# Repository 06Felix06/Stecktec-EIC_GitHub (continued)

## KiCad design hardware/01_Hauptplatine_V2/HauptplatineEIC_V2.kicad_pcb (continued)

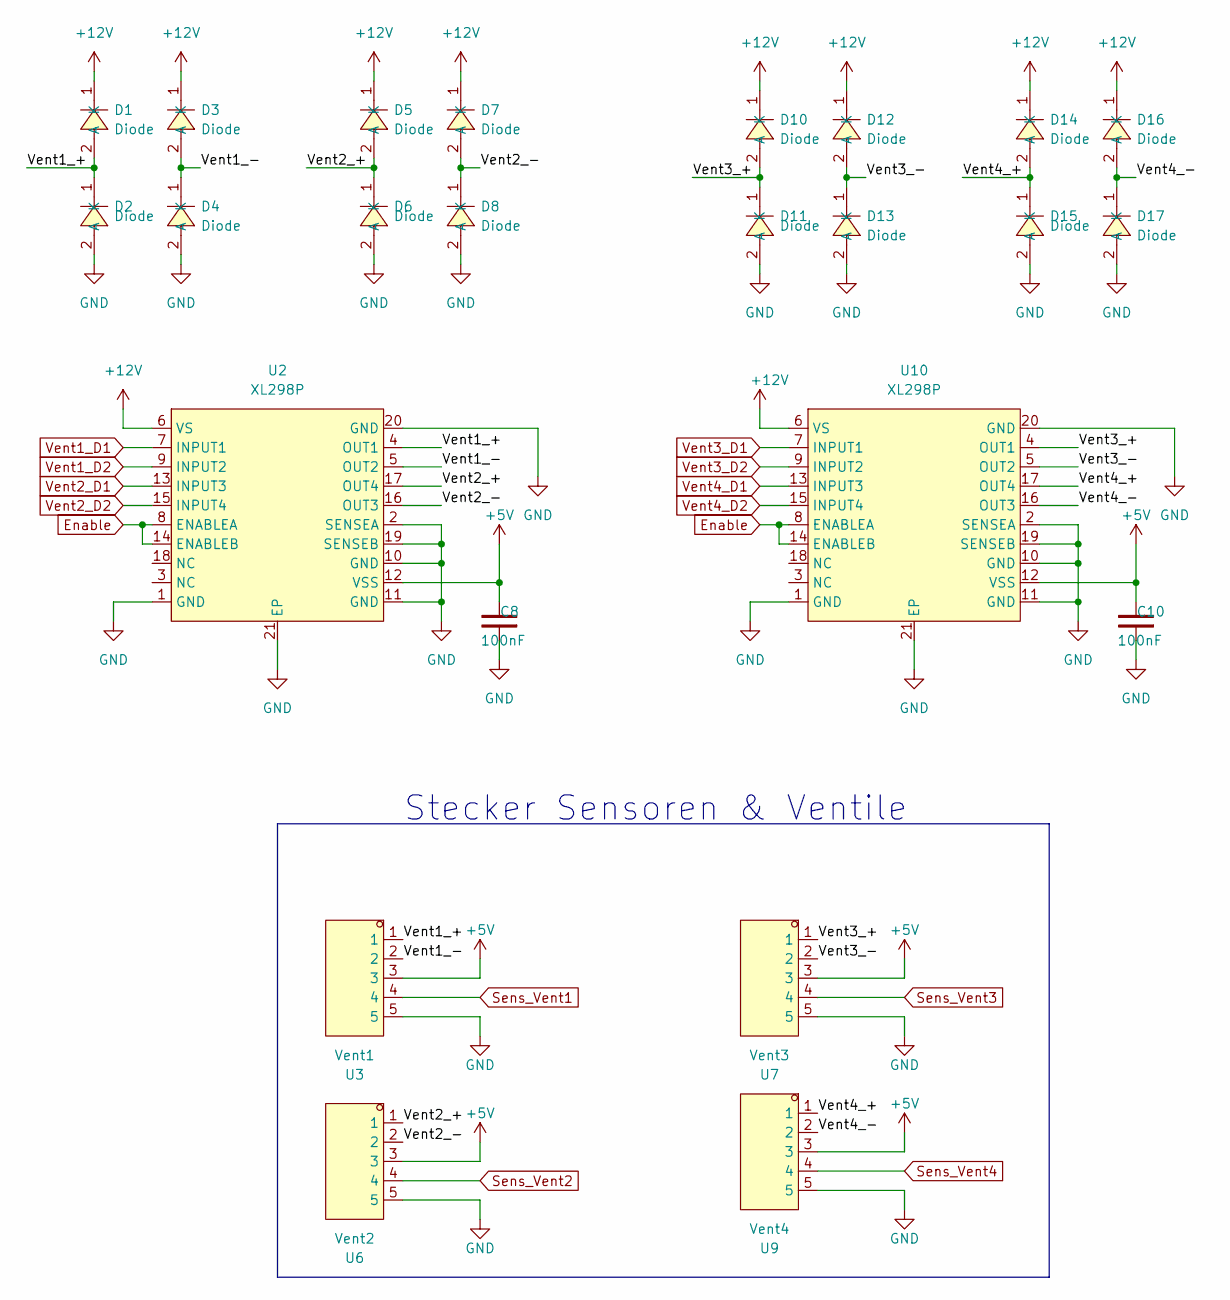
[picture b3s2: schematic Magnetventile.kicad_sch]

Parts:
C8, C10: 100nF; C_0805_2012Metric
D1, D2, D3, D4, D5, D6, D7, D8, D10, D11, D12, D13, D14, D15, D16, D17: Diode; SMA_L4.3-W2.5-LS5.0-RD; LCSC Part C727081
U2, U10: XL298P; HSOP-20_L15.9-W11.0-P1.27-LS14.2-BL-EP; LCSC Part C17179540
U3: Vent1; CONN-TH_B5B-PH-K-S-LF-SN; LCSC Part C157993
U6: Vent2; CONN-TH_B5B-PH-K-S-LF-SN; LCSC Part C157993
U7: Vent3; CONN-TH_B5B-PH-K-S-LF-SN; LCSC Part C157993
U9: Vent4; CONN-TH_B5B-PH-K-S-LF-SN; LCSC Part C157993

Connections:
+5V: C8.1, C10.1, U2.12 (VSS), U3.3, U6.3, U7.3, U9.3, U10.12 (VSS); also elsewhere on the board
+12V: D1.1 (K), D3.1 (K), D5.1 (K), D7.1 (K), D10.1 (K), D12.1 (K), D14.1 (K), D16.1 (K), U2.6 (VS), U10.6 (VS); also elsewhere on the board
/Magnetventile/Vent1_+: D1.2 (A), D2.1 (K), U2.4 (OUT1), U3.1
/Magnetventile/Vent1_-: D3.2 (A), D4.1 (K), U2.5 (OUT2), U3.2
/Magnetventile/Vent2_+: D5.2 (A), D6.1 (K), U2.17 (OUT4), U6.1
/Magnetventile/Vent2_-: D7.2 (A), D8.1 (K), U2.16 (OUT3), U6.2
/Magnetventile/Vent3_+: D10.2 (A), D11.1 (K), U7.1, U10.4 (OUT1)
/Magnetventile/Vent3_-: D12.2 (A), D13.1 (K), U7.2, U10.5 (OUT2)
/Magnetventile/Vent4_+: D14.2 (A), D15.1 (K), U9.1, U10.17 (OUT4)
/Magnetventile/Vent4_-: D16.2 (A), D17.1 (K), U9.2, U10.16 (OUT3)
Enable: U2.8 (ENABLEA), U2.14 (ENABLEB), U10.8 (ENABLEA), U10.14 (ENABLEB); also elsewhere on the board
GND: C8.2, C10.2, D2.2 (A), D4.2 (A), D6.2 (A), D8.2 (A), D11.2 (A), D13.2 (A), D15.2 (A), D17.2 (A), U2.1 (GND), U2.2 (SENSEA), U2.10 (GND), U2.11 (GND), U2.19 (SENSEB), U2.20 (GND), U2.21 (EP), U3.5, U6.5, U7.5, U9.5, U10.1 (GND), U10.2 (SENSEA), U10.10 (GND), U10.11 (GND), U10.19 (SENSEB), U10.20 (GND), U10.21 (EP); also elsewhere on the board
Sens_Vent1: U3.4; also elsewhere on the board
Sens_Vent2: U6.4; also elsewhere on the board
Sens_Vent3: U7.4; also elsewhere on the board
Sens_Vent4: U9.4; also elsewhere on the board
Vent1_D1: U2.7 (INPUT1); also elsewhere on the board
Vent1_D2: U2.9 (INPUT2); also elsewhere on the board
Vent2_D1: U2.13 (INPUT3); also elsewhere on the board
Vent2_D2: U2.15 (INPUT4); also elsewhere on the board
Vent3_D1: U10.7 (INPUT1); also elsewhere on the board
Vent3_D2: U10.9 (INPUT2); also elsewhere on the board
Vent4_D1: U10.13 (INPUT3); also elsewhere on the board
Vent4_D2: U10.15 (INPUT4); also elsewhere on the board

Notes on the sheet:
Stecker Sensoren & Ventile

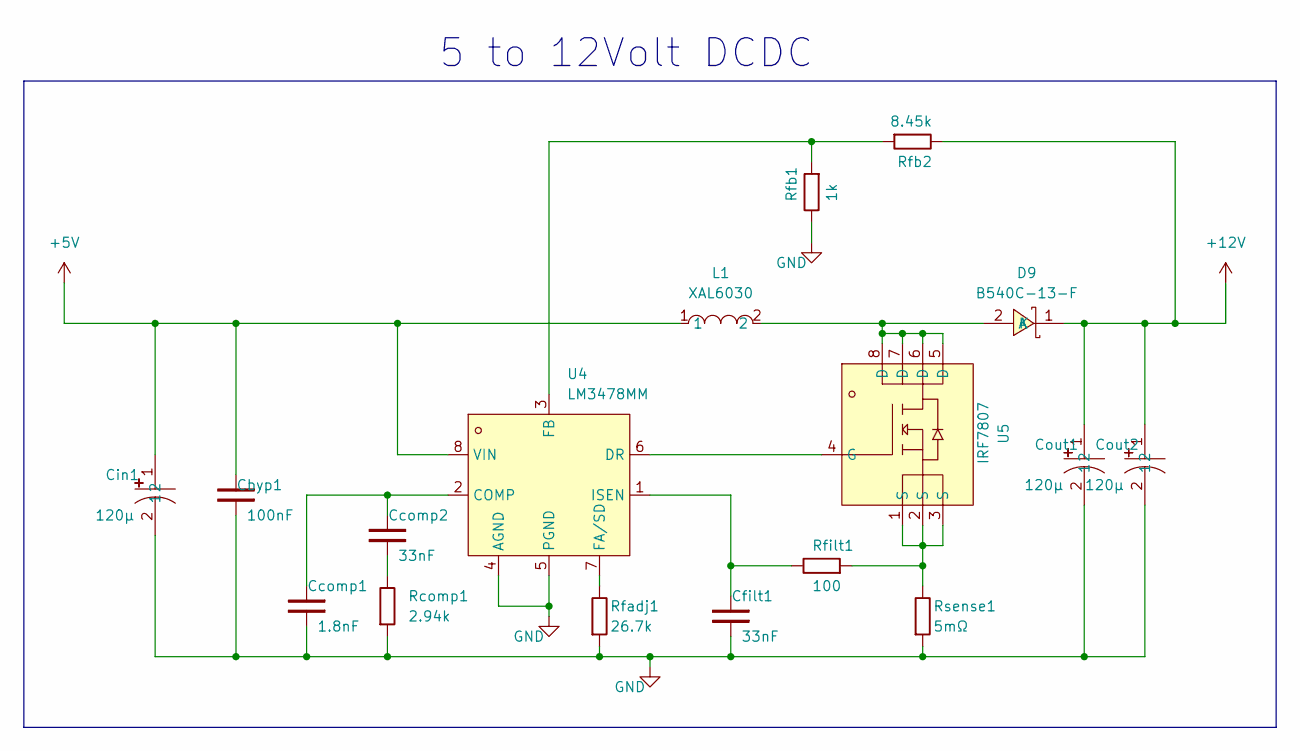
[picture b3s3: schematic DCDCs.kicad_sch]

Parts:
Cbyp1: 100nF; C_0805_2012Metric
Ccomp1: 1.8nF; C_0805_2012Metric
Ccomp2: 33nF; C_0805_2012Metric
Cfilt1: 33nF; C_0805_2012Metric
Cin1: 120µ; CAP-TH_BD6.3-P2.50-D1.0-FD; LCSC Part C442997
Cout1, Cout2: 120µ; CAP-TH_BD6.3-P2.50-D1.0-FD; LCSC Part C442997
D9: B540C-13-F; SMC_L7.1-W6.2-LS8.1-RD; LCSC Part C72264
L1: XAL6030; IND-SMD_L6.6-W6.4; LCSC Part C19191693
Rcomp1: 2.94k; R_0805_2012Metric
Rfadj1: 26.7k; R_0805_2012Metric
Rfb1: 1k; R_0805_2012Metric
Rfb2: 8.45k; R_0805_2012Metric
Rfilt1: 100; R_0805_2012Metric
Rsense1: 5mΩ; R_0805_2012Metric
U4: LM3478MM; VSSOP-8_L3.0-W3.0-P0.65-LS5.0-BL; LCSC Part C9404
U5: IRF7807; SOP-8_L4.9-W3.9-P1.27-LS6.0-BL; LCSC Part C5350865

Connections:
+5V: Cbyp1.1, Cin1.1, L1.1, U4.8 (VIN); also elsewhere on the board
+12V: Cout1.1, Cout2.1, D9.1 (K), Rfb2.2; also elsewhere on the board
GND: Cbyp1.2, Ccomp1.2, Cfilt1.2, Cin1.2, Cout1.2, Cout2.2, Rcomp1.1, Rfadj1.1, Rfb1.2, Rsense1.1, U4.4 (AGND), U4.5 (PGND); also elsewhere on the board
unnamed: Ccomp2.2, Rcomp1.2
unnamed: D9.2 (A), L1.2, U5.5 (D), U5.6 (D), U5.7 (D), U5.8 (D)
unnamed: Rfilt1.1, Rsense1.2, U5.1 (S), U5.2 (S), U5.3 (S)
unnamed: Ccomp1.1, Ccomp2.1, U4.2 (COMP)
unnamed: U4.6 (DR), U5.4 (G)
unnamed: Rfadj1.2, U4.7 (FA/SD)
unnamed: Rfb1.1, Rfb2.1, U4.3 (FB)
unnamed: Cfilt1.1, Rfilt1.2, U4.1 (ISEN)

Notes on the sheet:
5 to 12Volt DCDC

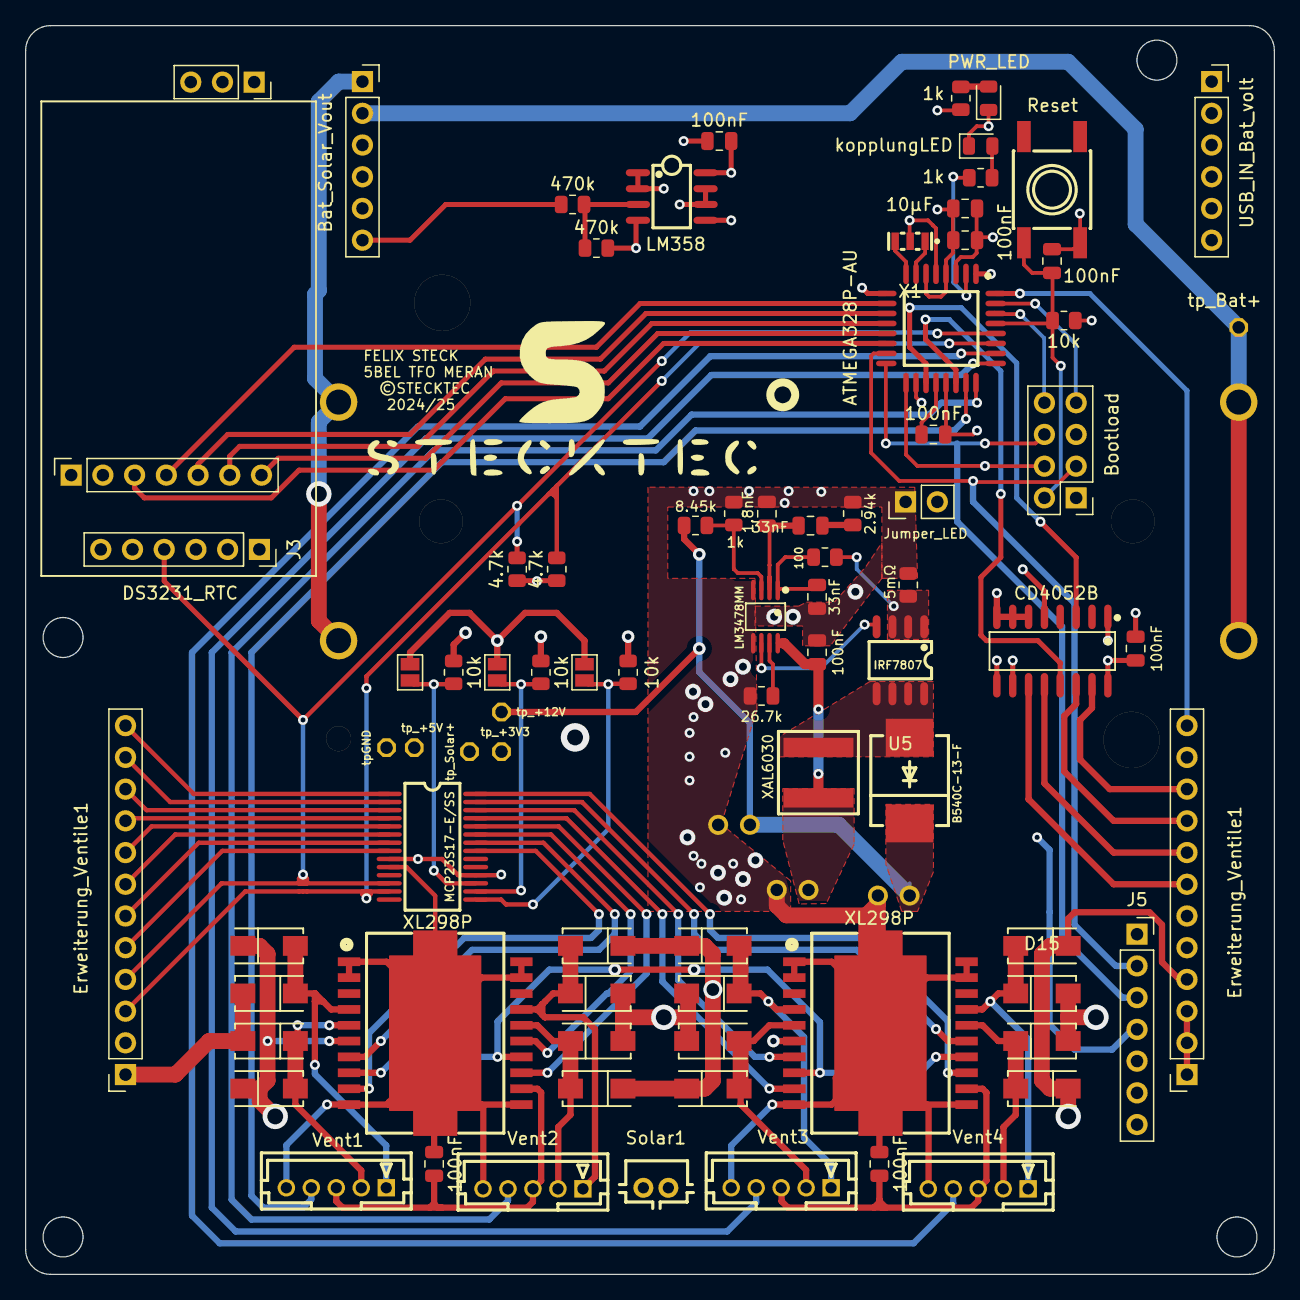
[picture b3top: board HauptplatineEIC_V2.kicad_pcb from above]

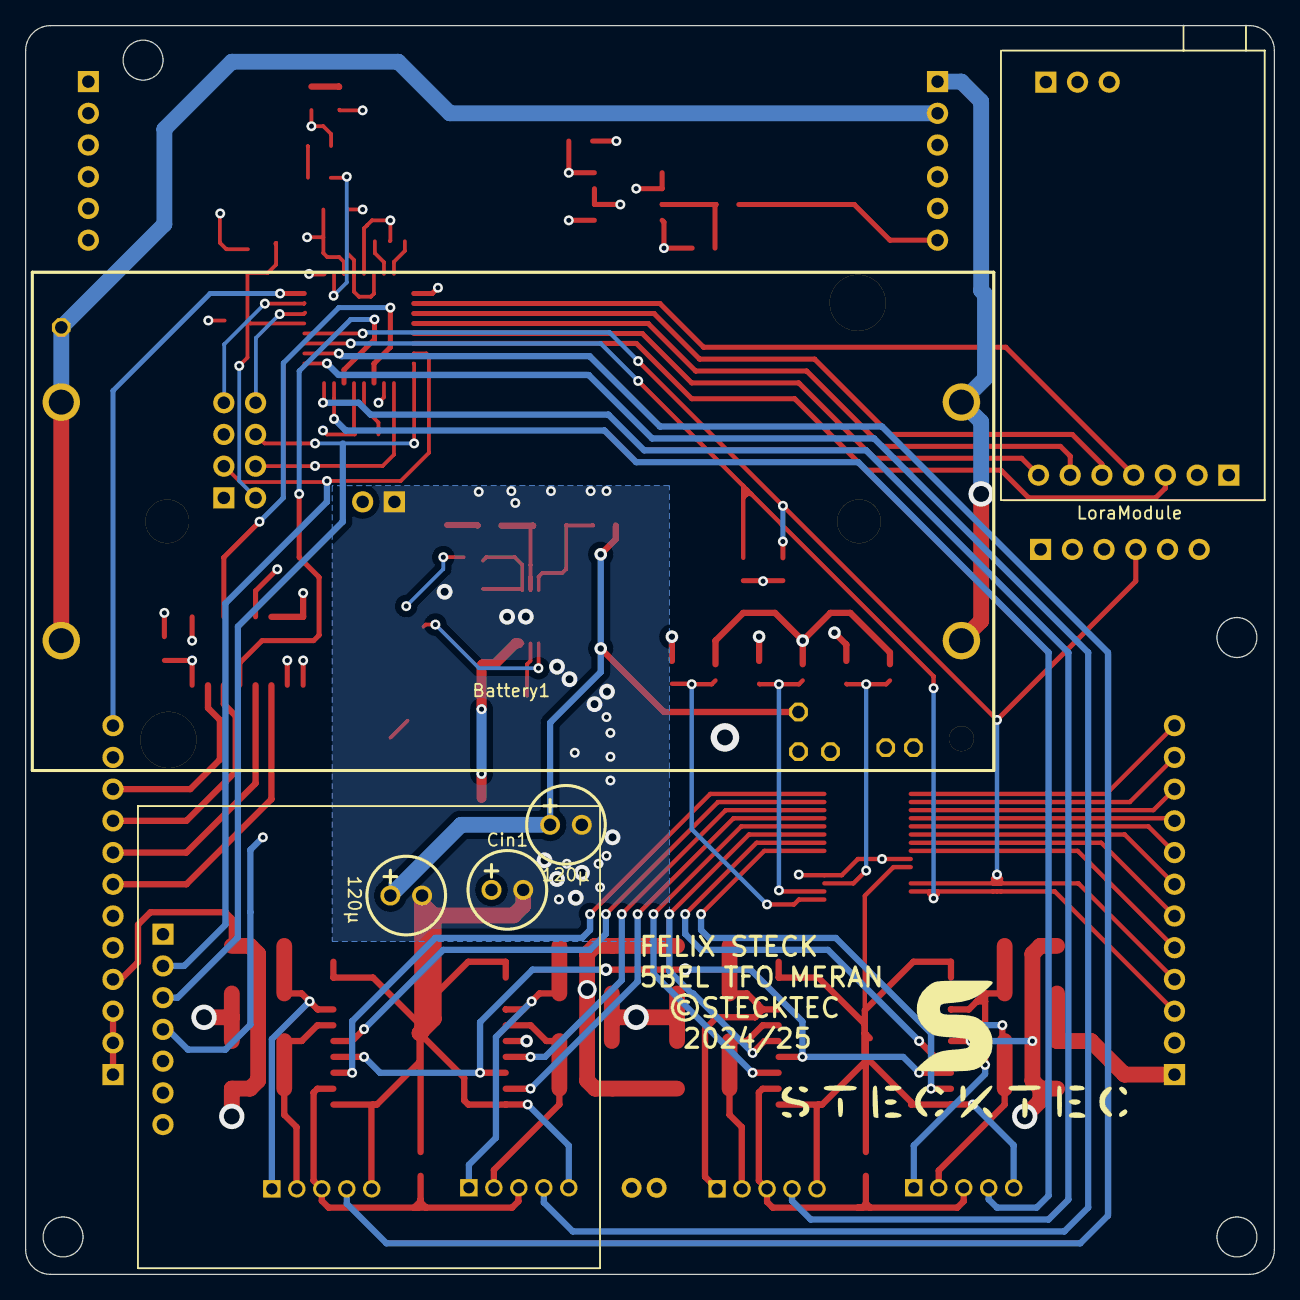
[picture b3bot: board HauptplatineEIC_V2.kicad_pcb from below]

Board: 6 copper layers, 100.0 x 100.0 mm, 86 parts (4 on the bottom side), 80 nets.

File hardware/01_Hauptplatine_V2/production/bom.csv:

Designator,Footprint,Quantity,Value,LCSC Part #
Battery1,BAT-TH_L77.0-W39.9_BH-18650-A1BJ021,1,BH-18650-A1BJ021,C20606804
"C1, C10, C2, C4, C5, C6, C8, Cbyp1",0805,8,100nF,
C3,0805,1,10µF,
Ccomp1,0805,1,1.8nF,
"Ccomp2, Cfilt1",0805,2,33nF,
"Cin1, Cout1, Cout2",CAP-TH_BD6.3-P2.50-D1.0-FD,3,120µ,C442997
"D1, D10, D11, D12, D13, D14, D15, D16, D17, D2, D3, D4, D5, D6, D7, D8",SMA_L4.3-W2.5-LS5.0-RD,16,Diode,C727081
D30,0805,1,kopplungLED,
D31,0805,1,PWR_LED,
D9,SMC_L7.1-W6.2-LS8.1-RD,1,B540C-13-F,C72264
J1,PinSocket_1x07_P2.54mm_Vertical,1,LoraModule,
J15,PinHeader_1x02_P2.54mm_Vertical,1,Jumper_LED,
J17,PinSocket_1x03_P2.54mm_Vertical,1,Befestigung,
J2,PinHeader_2x04_P2.54mm_Vertical,1,Bootload,
"J20, J4",PinSocket_1x12_P2.54mm_Vertical,2,Erweiterung_Ventile1,
J3,PinSocket_1x06_P2.54mm_Vertical,1,DS3231_RTC,
J5,PinSocket_1x07_P2.54mm_Vertical,1,Sim7000,
J7,PinSocket_1x06_P2.54mm_Vertical,1,USB_IN_Bat_volt,
J8,PinSocket_1x06_P2.54mm_Vertical,1,Bat_Solar_Vout,
"JP4, JP5, JP6",SolderJumper-2_P1.3mm_Open_Pad1.0x1.5mm,3,SolderJumper_2_Open,
L1,IND-SMD_L6.6-W6.4,1,XAL6030,C19191693
"R1, R6, R7, R8",0805,4,10k,
"R2, R3",0805,2,470k,
"R4, R5",0805,2,4.7k,
"RV_LED1, RV_LED2, Rfb1",0805,3,1k,
Rcomp1,0805,1,2.94k,
Reset1,SW-SMD_4P-L6.2-W6.2-P4.50-LS8.6,1,Reset,C2909692
Rfadj1,0805,1,26.7k,
Rfb2,0805,1,8.45k,
Rfilt1,0805,1,100,
Rsense1,0805,1,5mΩ,
Solar1,CONN-TH_B2B-PH-K-S,1,B2B-PH-K-S(LF)(SN),C131337
TP1,TPSteckFelix,1,tp_Bat+,
TP2,TPSteckFelix,1,tp_Solar+,
TP3,TPSteckFelix,1,tp_+5V,
TP4,TPSteckFelix,1,tp_+3V3,
TP5,TPSteckFelix,1,tpGND,
TP6,TPSteckFelix,1,tp_+12V,
U1,TQFP-32_L7.0-W7.0-P0.80-LS9.0-BL,1,ATMEGA328P-AU,C14877
"U10, U2",HSOP-20_L15.9-W11.0-P1.27-LS14.2-BL-EP,2,XL298P,C17179540
U11,SOIC-8_L5.0-W4.0-P1.27-LS6.0-BL,1,LM358,
U12,SSOP-28_L10.2-W5.3-P0.65-LS7.8-BL,1,MCP23S17-E/SS,C148009
U3,CONN-TH_B5B-PH-K-S-LF-SN,1,Vent1,C157993
U4,VSSOP-8_L3.0-W3.0-P0.65-LS5.0-BL,1,LM3478MM,C9404
U5,SOP-8_L4.9-W3.9-P1.27-LS6.0-BL,1,IRF7807,C5350865
U6,CONN-TH_B5B-PH-K-S-LF-SN,1,Vent2,C157993
U7,CONN-TH_B5B-PH-K-S-LF-SN,1,Vent3,C157993
U8,SOIC-16_L9.9-W3.9-P1.27-LS6.0-BL,1,CD4052B,C5356105
U9,CONN-TH_B5B-PH-K-S-LF-SN,1,Vent4,C157993
X1,OSC-SMD_3P-L3.2-W1.3-P1.20-L,1,CSTNE16M0V53Z000R0,C783275

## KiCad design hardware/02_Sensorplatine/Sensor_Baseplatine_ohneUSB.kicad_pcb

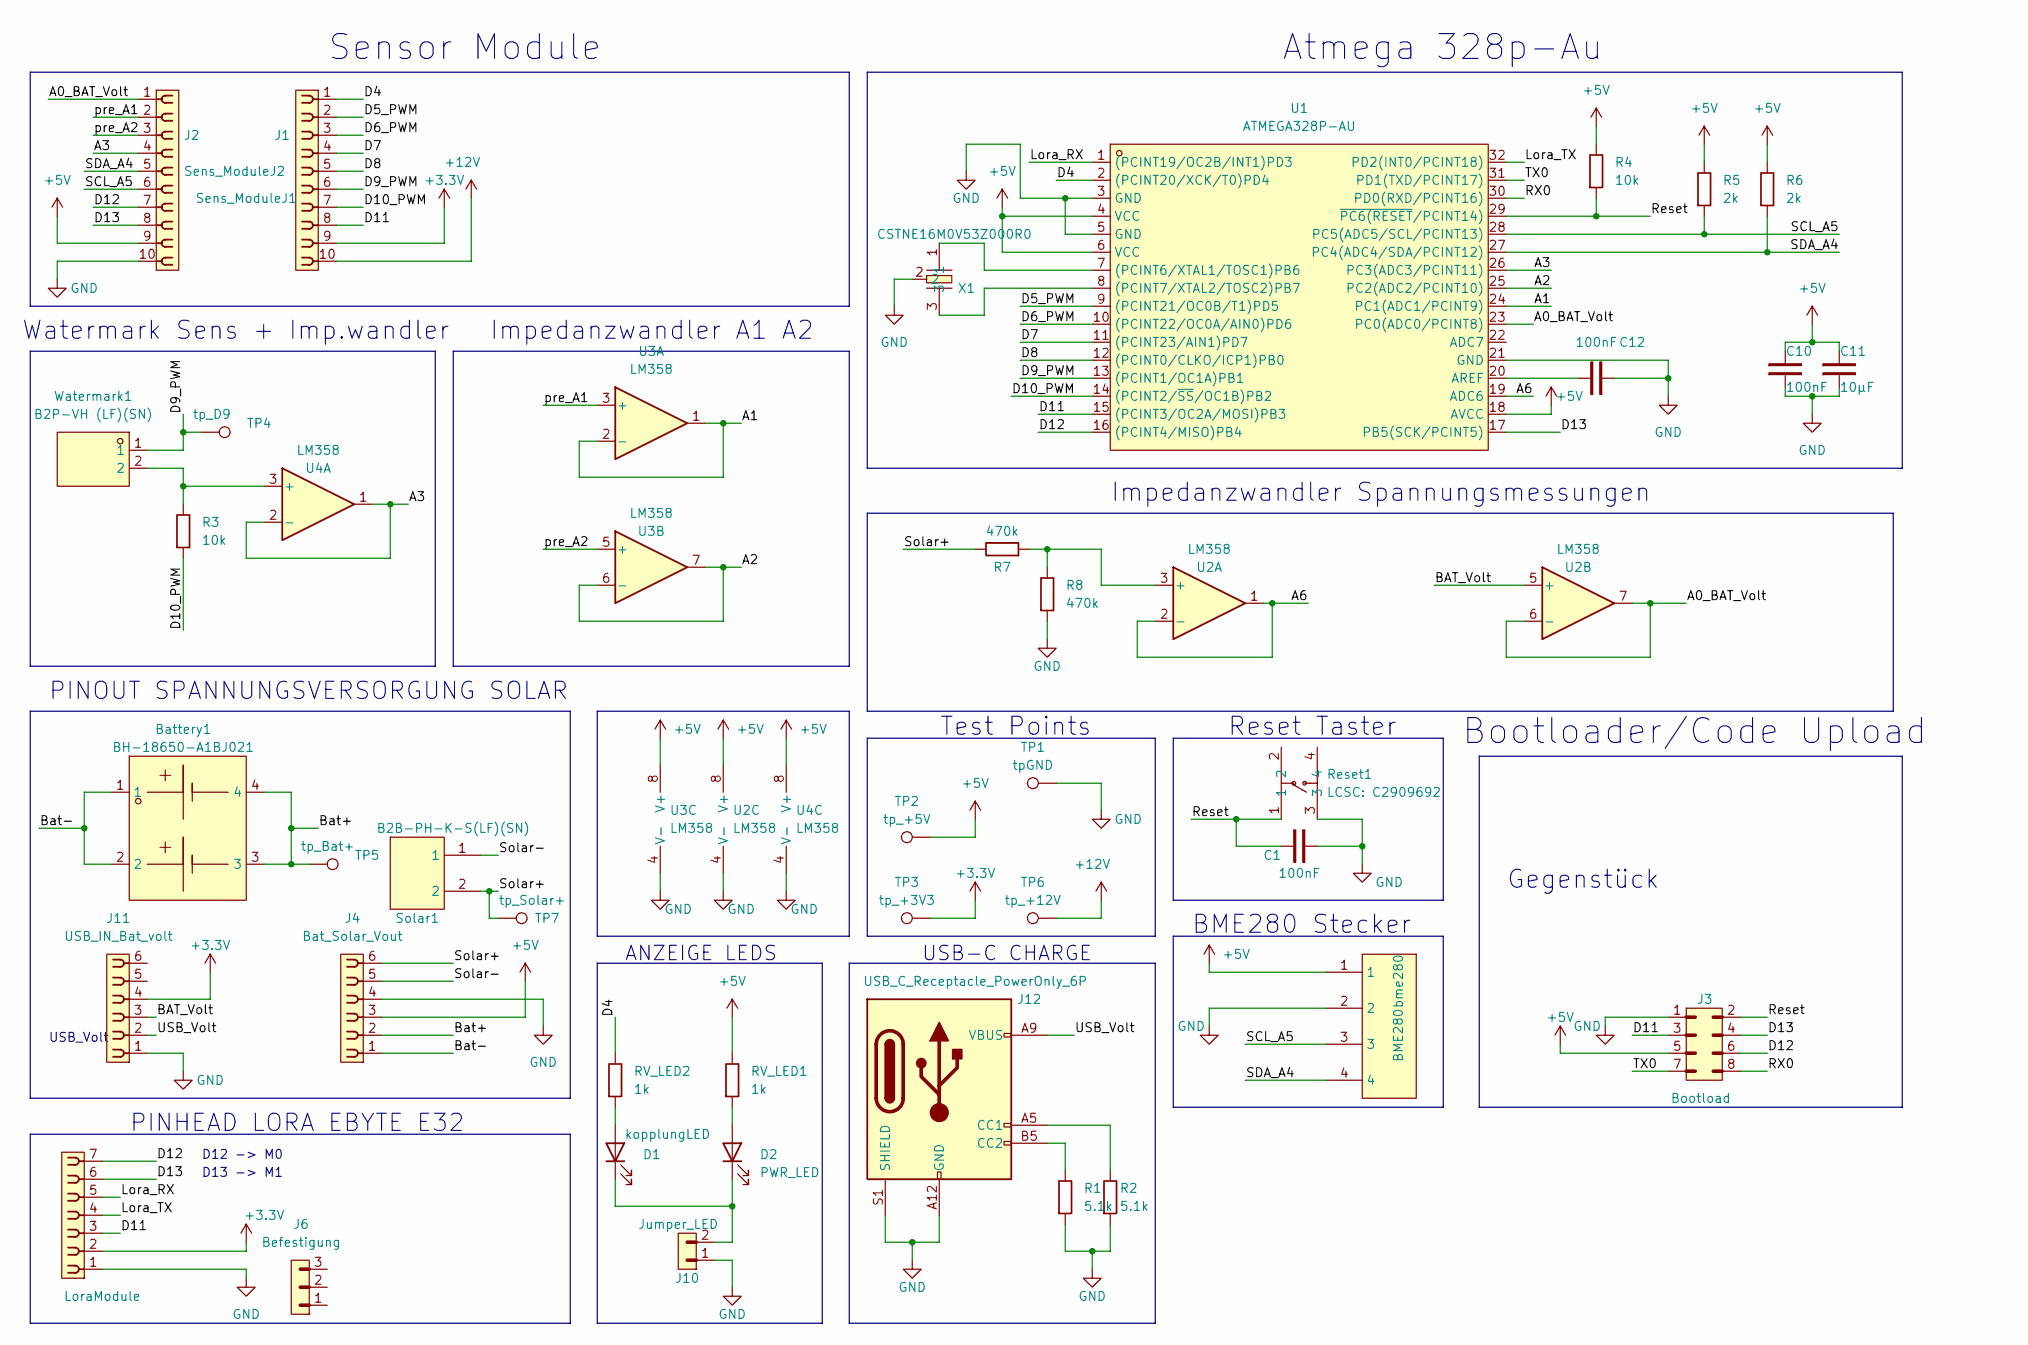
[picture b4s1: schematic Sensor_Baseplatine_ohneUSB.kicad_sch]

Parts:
Battery1: BH-18650-A1BJ021; BAT-TH_L77.0-W39.9_BH-18650-A1BJ021; LCSC Part C20606804
C1, C10, C12: 100nF; C_0805_2012Metric
C11: 10µF; C_0805_2012Metric
D1: kopplungLED; LED_0805_2012Metric
D2: PWR_LED; LED_0805_2012Metric
J1: Sens_ModuleJ1; PinSocket_1x10_P2.54mm_Vertical
J2: Sens_ModuleJ2; PinSocket_1x10_P2.54mm_Vertical
J3: Bootload; PinHeader_2x04_P2.54mm_Vertical
J4: Bat_Solar_Vout; PinSocket_1x06_P2.54mm_Vertical
J5: LoraModule; PinSocket_1x07_P2.54mm_Vertical
J6: Befestigung; PinHeader_1x03_P2.54mm_Vertical
J10: Jumper_LED; PinHeader_1x02_P2.54mm_Vertical
J11: USB_IN_Bat_volt; PinSocket_1x06_P2.54mm_Vertical
J12: USB_C_Receptacle_PowerOnly_6P; USB_C_Receptacle_GCT_USB4125-xx-x_6P_TopMnt_Horizontal
R1, R2: 5.1k; R_0805_2012Metric
R3, R4: 10k; R_0805_2012Metric
R5, R6: 2k; R_0805_2012Metric
R7, R8: 470k; R_0805_2012Metric
RV_LED1, RV_LED2: 1k; R_0805_2012Metric
Reset1: LCSC: C2909692; SW-SMD_4P-L6.2-W6.2-P4.50-LS8.6; LCSC Part C2909692
Solar1: B2B-PH-K-S(LF)(SN); CONN-TH_B2B-PH-K-S; LCSC Part C131337
TP1: tpGND; TPSteckFelix
TP2: tp_+5V; TPSteckFelix
TP3: tp_+3V3; TPSteckFelix
TP4: tp_D9; TPSteckFelix
TP5: tp_Bat+; TPSteckFelix
TP6: tp_+12V; TPSteckFelix
TP7: tp_Solar+; TPSteckFelix
U1: ATMEGA328P-AU; TQFP-32_L7.0-W7.0-P0.80-LS9.0-BL; LCSC Part C14877
U2, U3, U4: LM358; SOIC-8_L5.0-W4.0-P1.27-LS6.0-BL
Watermark1: B2P-VH (LF)(SN); CONN-TH_B2P-VH-LF-SN; LCSC Part C160315
X1: CSTNE16M0V53Z000R0; OSC-SMD_3P-L3.2-W1.3-P1.20-L; LCSC Part C783275
bme280: BME280; CONN-TH_B4B-PH-K-S; LCSC Part C131334

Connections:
+3.3V: J1.9, J5.2, J11.4, TP3.1
+5V: C10.2, C11.2, J2.9, J3.5, J4.3, R4.2, R5.2, R6.2, RV_LED1.2, TP2.1, U1.4 (VCC), U1.6 (VCC), U1.18 (AVCC), U2.8 (V+), U3.8 (V+), U4.8 (V+), bme280.1
+12V: J1.10, TP6.1
/A0_BAT_Volt: J2.1, U1.23 (PC0(ADC0/PCINT8)), U2.6 (-), U2.7
/A1: U1.24 (PC1(ADC1/PCINT9)), U3.1, U3.2 (-)
/A2: U1.25 (PC2(ADC2/PCINT10)), U3.6 (-), U3.7
/A3: J2.4, U1.26 (PC3(ADC3/PCINT11)), U4.1, U4.2 (-)
/A6: U1.19 (ADC6), U2.1, U2.2 (-)
/BAT_Volt: J11.3, U2.5 (+)
/Bat+: Battery1.3, Battery1.4, J4.2, TP5.1
/Bat-: Battery1.1, Battery1.2, J4.1
/D4: J1.1, RV_LED2.2, U1.2 ((PCINT20/XCK/T0)PD4)
/D5_PWM: J1.2, U1.9 ((PCINT21/OC0B/T1)PD5)
/D6_PWM: J1.3, U1.10 ((PCINT22/OC0A/AIN0)PD6)
/D7: J1.4, U1.11 ((PCINT23/AIN1)PD7)
/D8: J1.5, U1.12 ((PCINT0/CLKO/ICP1)PB0)
/D9_PWM: J1.6, TP4.1, U1.13 ((PCINT1/OC1A)PB1), Watermark1.1
/D10_PWM: J1.7, R3.1, U1.14 ((PCINT2/~SS/OC1B)PB2)
/D11: J1.8, J3.3, J5.3, U1.15 ((PCINT3/OC2A/MOSI)PB3)
/D12: J2.7, J3.6, J5.7, U1.16 ((PCINT4/MISO)PB4)
/D13: J2.8, J3.4, J5.6, U1.17 (PB5(SCK/PCINT5))
/Lora_RX: J5.5, U1.1 ((PCINT19/OC2B/INT1)PD3)
/Lora_TX: J5.4, U1.32 (PD2(INT0/PCINT18))
/RX0: J3.8, U1.30 (PD0(RXD/PCINT16))
/Reset: C1.1, J3.2, R4.1, Reset1.1, U1.29 (~PC6(RESET/PCINT14))
/SCL_A5: J2.6, R5.1, U1.28 (PC5(ADC5/SCL/PCINT13)), bme280.3
/SDA_A4: J2.5, R6.1, U1.27 (PC4(ADC4/SDA/PCINT12)), bme280.4
/Solar+: J4.6, R7.2, Solar1.2, TP7.1
/Solar-: J4.5, Solar1.1
/TX0: J3.7, U1.31 (PD1(TXD/PCINT17))
/USB_Volt: J11.2, J12.A9 (VBUS), J12.B9 (VBUS)
/pre_A1: J2.2, U3.3 (+)
/pre_A2: J2.3, U3.5 (+)
GND: C1.2, C10.1, C11.1, C12.1, J2.10, J3.1, J4.4, J5.1, J10.1, J11.1, J12.A12 (GND), J12.B12 (GND), J12.S1 (SHIELD), R1.1, R2.1, R8.1, Reset1.3, TP1.1, U1.3 (GND), U1.5 (GND), U1.21 (GND), U2.4 (V-), U3.4 (V-), U4.4 (V-), X1.2, bme280.2
unnamed: D1.2 (A), RV_LED2.1
unnamed: D1.1 (K), D2.1 (K), J10.2
unnamed: D2.2 (A), RV_LED1.1
unnamed: J12.A5 (CC1), R2.2
unnamed: J12.B5 (CC2), R1.2
unnamed: U1.7 ((PCINT6/XTAL1/TOSC1)PB6), X1.1
unnamed: U1.8 ((PCINT7/XTAL2/TOSC2)PB7), X1.3
unnamed: C12.2, U1.20 (AREF)
unnamed: R7.1, R8.2, U2.3 (+)
unnamed: R3.2, U4.3 (+), Watermark1.2

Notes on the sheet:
Gegenstück
Atmega 328p-Au
PINHEAD LORA EBYTE E32
USB-C CHARGE
Impedanzwandler Spannungsmessungen
Reset Taster
Watermark Sens + Imp.wandler
PINOUT SPANNUNGSVERSORGUNG SOLAR
D13 -> M1
Sensor Module
ANZEIGE LEDS
Bootloader/Code Upload
USB_Volt
Test Points
D12 -> M0
Impedanzwandler A1 A2
BME280 Stecker

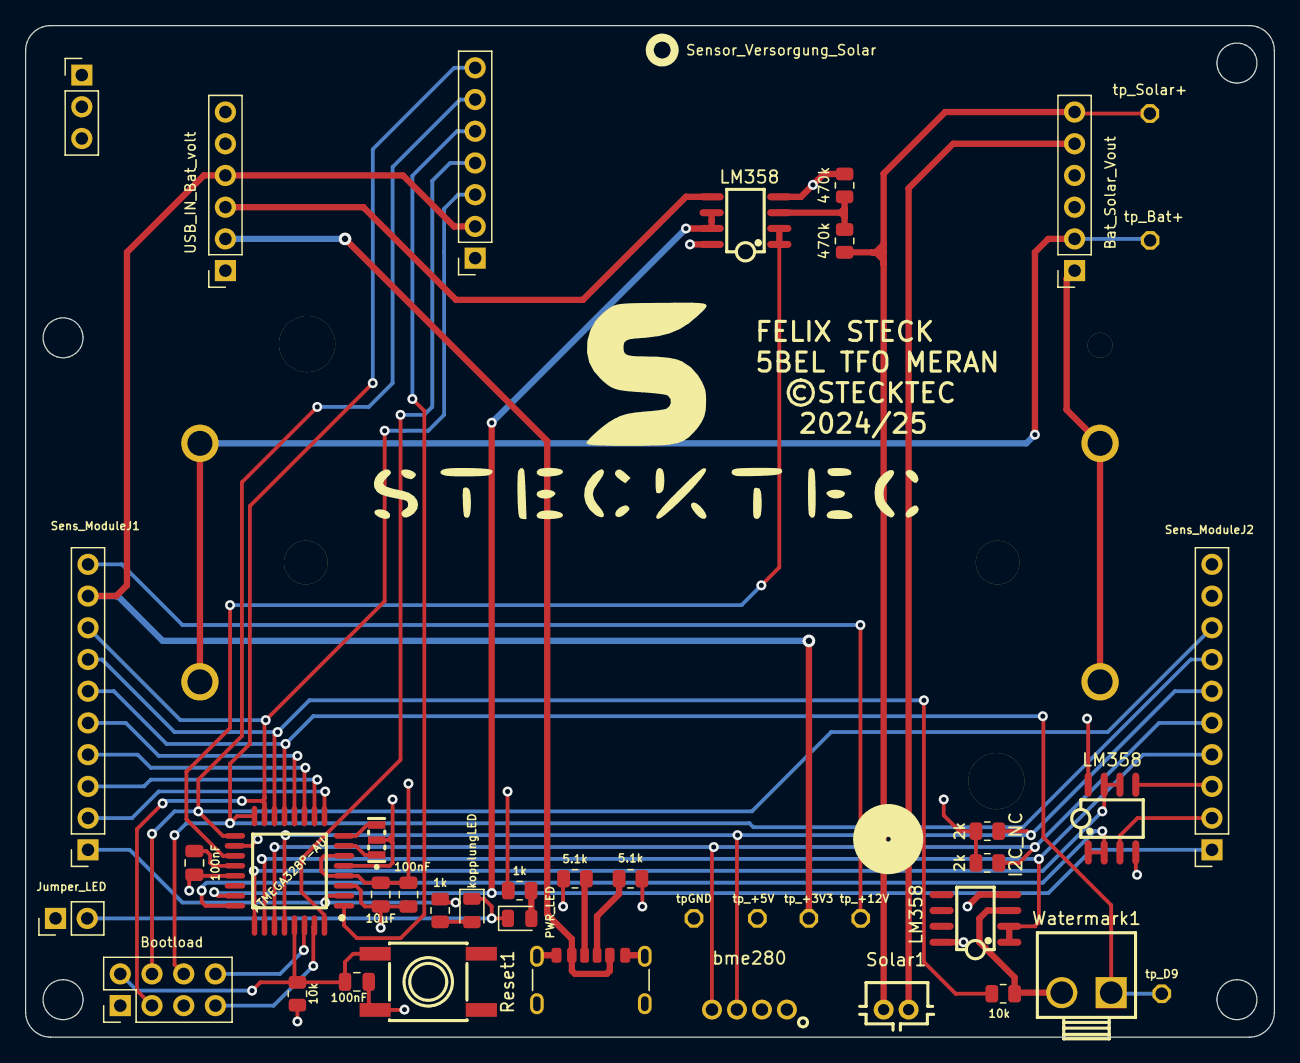
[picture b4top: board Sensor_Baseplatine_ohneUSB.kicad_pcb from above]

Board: 4 copper layers, 100.0 x 81.0 mm, 42 parts (1 on the bottom side), 44 nets.

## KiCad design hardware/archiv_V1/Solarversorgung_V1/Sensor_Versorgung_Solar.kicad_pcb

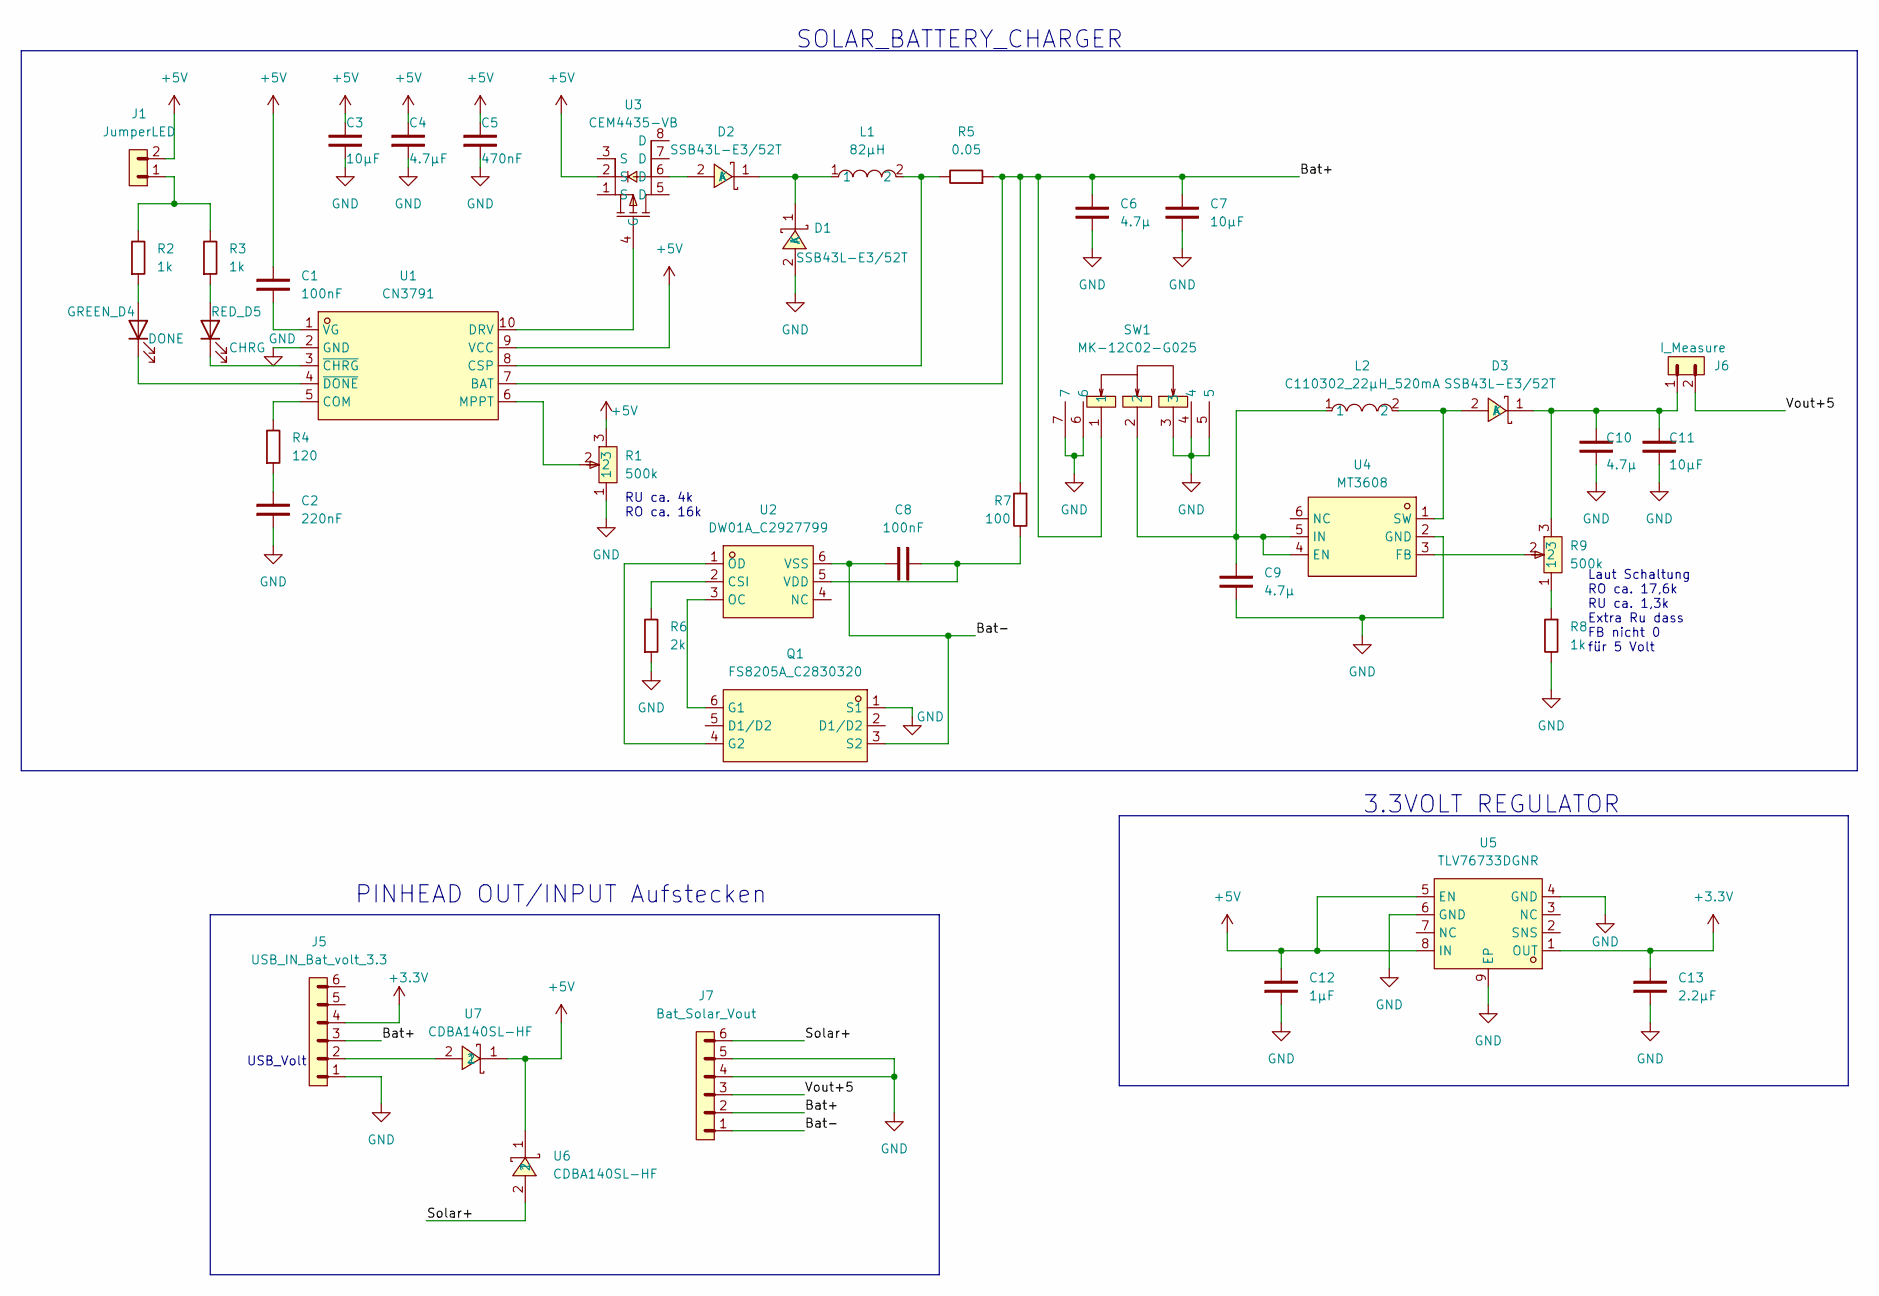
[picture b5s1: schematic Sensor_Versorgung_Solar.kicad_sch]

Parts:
C1, C8: 100nF; C_0805_2012Metric
C2: 220nF; C_0805_2012Metric
C3, C7, C11: 10µF; C_0805_2012Metric
C4: 4.7µF; C_0805_2012Metric
C5: 470nF; C_0805_2012Metric
C6, C9, C10: 4.7µ; C_0805_2012Metric
C12: 1µF; C_0805_2012Metric
C13: 2.2µF; C_0805_2012Metric
D1, D2, D3: SSB43L-E3/52T; SMB_L4.6-W3.6-LS5.3-RD; LCSC Part C222519
GREEN_D4: DONE; LED_0805_2012Metric
J1: JumperLED; PinHeader_1x02_P2.54mm_Vertical
J5: USB_IN_Bat_volt_3.3; PinHeader_1x06_P2.54mm_Vertical
J6: I_Measure; PinHeader_1x02_P2.54mm_Vertical
J7: Bat_Solar_Vout; PinHeader_1x06_P2.54mm_Vertical
L1: 82µH; IND-SMD_L3.5-W2.9_FHW1210IF820JST; LCSC Part C394099
L2: C110302_22µH_520mA; IND-SMD_L3.0-W3.0_LQH3NPN; LCSC Part C110302
Q1: FS8205A_C2830320; SOT-23-6_L2.9-W1.6-P0.95-LS2.8-BR; LCSC Part C2830320
R1, R9: 500k; RES-ADJ-SMD_VG039NCH; LCSC Part C128558
R2, R3, R8: 1k; R_0805_2012Metric
R4: 120; R_0805_2012Metric
R5: 0.05; R_0805_2012Metric
R6: 2k; R_0805_2012Metric
R7: 100; R_0805_2012Metric
RED_D5: CHRG; LED_0805_2012Metric
SW1: MK-12C02-G025; SW-SMD_MK-12C02-G025; LCSC Part C778186
U1: CN3791; SSOP-10_L4.9-W3.9-P1.00-LS6.0-BL; LCSC Part C154992
U2: DW01A_C2927799; SOT-23-6_L2.9-W1.6-P0.95-LS2.8-BL; LCSC Part C2927799
U3: CEM4435-VB; SOIC-8_L4.9-W3.9-P1.27-LS6.0-BL; LCSC Part C5137442
U4: MT3608; SOT-23-6_L2.9-W1.6-P0.95-LS2.8-BL; LCSC Part C84817
U5: TLV76733DGNR; MSOP-8_L3.0-W3.0-P0.65-LS4.9-BL-EP-1; LCSC Part C2873382
U6, U7: CDBA140SL-HF; DO-214AC_L4.3-W2.7-LS5.3-RD; LCSC Part C3012747

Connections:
+3.3V: C13.2, J5.4, U5.1 (OUT)
+5V: C1.2, C3.1, C4.2, C5.2, C12.2, J1.2, R1.3, U1.9 (VCC), U3.2 (S), U5.5 (EN), U5.8 (IN), U6.1, U7.1
/Bat+: C6.1, C7.1, J5.3, J7.2, R5.1, R7.1, SW1.1, U1.7 (BAT)
/Bat-: C8.1, J7.1, Q1.3 (S2), U2.6 (VSS)
/Solar+: J7.6, U6.2
/Vout+5: J6.2, J7.3
GND: C2.1, C3.2, C4.1, C5.1, C6.2, C7.2, C9.2, C10.2, C11.2, C12.1, C13.1, D1.2 (A), J5.1, J7.4, J7.5, Q1.1 (S1), R1.1, R6.1, R8.2, SW1.3, SW1.4, SW1.5, SW1.6, SW1.7, U1.2 (GND), U4.2 (GND), U5.4 (GND), U5.6 (GND), U5.9 (EP)
unnamed: C2.2, R4.1
unnamed: D1.1 (K), D2.1 (K), L1.1
unnamed: D2.2 (A), U3.6 (D)
unnamed: D3.2 (A), L2.2, U4.1 (SW)
unnamed: C10.1, C11.1, D3.1 (K), J6.1, R9.3
unnamed: GREEN_D4.2 (A), R2.1
unnamed: GREEN_D4.1 (K), U1.4 (~DONE)
unnamed: J1.1, R2.2, R3.2
unnamed: J5.2, U7.2
unnamed: Q1.6 (G1), U2.3 (OC)
unnamed: Q1.4 (G2), U2.1 (OD)
unnamed: R8.1, R9.1
unnamed: R3.1, RED_D5.2 (A)
unnamed: RED_D5.1 (K), U1.3 (~CHRG)
unnamed: R4.2, U1.5 (COM)
unnamed: L1.2, R5.2, U1.8 (CSP)
unnamed: U1.10 (DRV), U3.4 (G)
unnamed: R1.2, U1.6 (MPPT)
unnamed: C1.1, U1.1 (VG)
unnamed: R6.2, U2.2 (CSI)
unnamed: C8.2, R7.2, U2.5 (VDD)
unnamed: C9.1, L2.1, SW1.2, U4.4 (EN), U4.5 (IN)
unnamed: R9.2, U4.3 (FB)

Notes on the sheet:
PINHEAD OUT/INPUT Aufstecken
RU ca. 4k RO ca. 16k
SOLAR_BATTERY_CHARGER
Laut Schaltung RO ca. 17,6k RU ca. 1,3k Extra Ru dass FB nicht 0 für 5 Volt
3.3VOLT REGULATOR
USB_Volt

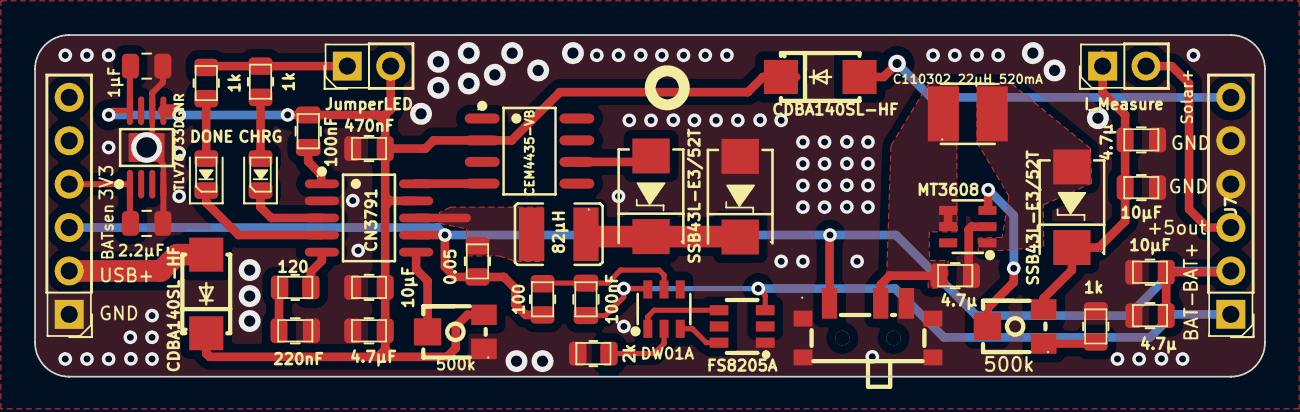
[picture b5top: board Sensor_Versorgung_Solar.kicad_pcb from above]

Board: 2 copper layers, 72.0 x 20.0 mm, 42 parts (0 on the bottom side), 30 nets.

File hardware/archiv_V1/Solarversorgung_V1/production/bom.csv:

Designator,Footprint,Quantity,Value,LCSC Part #
"C1, C8",0805,2,100nF,
"C10, C6, C9",0805,3,4.7µ,
"C11, C3, C7",0805,3,10µF,
C12,0805,1,1µF,
C13,0805,1,2.2µF,
C2,0805,1,220nF,
C4,0805,1,4.7µF,
C5,0805,1,470nF,
"D1, D2, D3",SMB_L4.6-W3.6-LS5.3-RD,3,SSB43L-E3/52T,C222519
GREEN_D4,0805,1,DONE,
J1,PinHeader_1x02_P2.54mm_Vertical,1,JumperLED,
J5,PinHeader_1x06_P2.54mm_Vertical,1,USB_IN_Bat_volt_3.3,
J6,PinHeader_1x02_P2.54mm_Vertical,1,I_Measure,
J7,PinHeader_1x06_P2.54mm_Vertical,1,Bat_Solar_Vout,
L1,IND-SMD_L3.5-W2.9_FHW1210IF820JST,1,82µH,C394099
L2,IND-SMD_L3.0-W3.0_LQH3NPN,1,C110302_22µH_520mA,C110302
Q1,SOT-23-6_L2.9-W1.6-P0.95-LS2.8-BR,1,FS8205A,C2830320
"R1, R9",RES-ADJ-SMD_VG039NCH,2,500k,C128558
"R2, R3, R8",0805,3,1k,
R4,0805,1,120,
R5,0805,1,0.05,
R6,0805,1,2k,
R7,0805,1,100,
RED_D5,0805,1,CHRG,
SW1,SW-SMD_MK-12C02-G025,1,MK-12C02-G025,C778186
U1,SSOP-10_L4.9-W3.9-P1.00-LS6.0-BL,1,CN3791,C154992
U2,SOT-23-6_L2.9-W1.6-P0.95-LS2.8-BL,1,DW01A,C2927799
U3,SOIC-8_L4.9-W3.9-P1.27-LS6.0-BL,1,CEM4435-VB,C5137442
U4,SOT-23-6_L2.9-W1.6-P0.95-LS2.8-BL,1,MT3608,C84817
U5,MSOP-8_L3.0-W3.0-P0.65-LS4.9-BL-EP-1,1,TLV76733DGNR,C2873382
"U6, U7",DO-214AC_L4.3-W2.7-LS5.3-RD,2,CDBA140SL-HF,C3012747
